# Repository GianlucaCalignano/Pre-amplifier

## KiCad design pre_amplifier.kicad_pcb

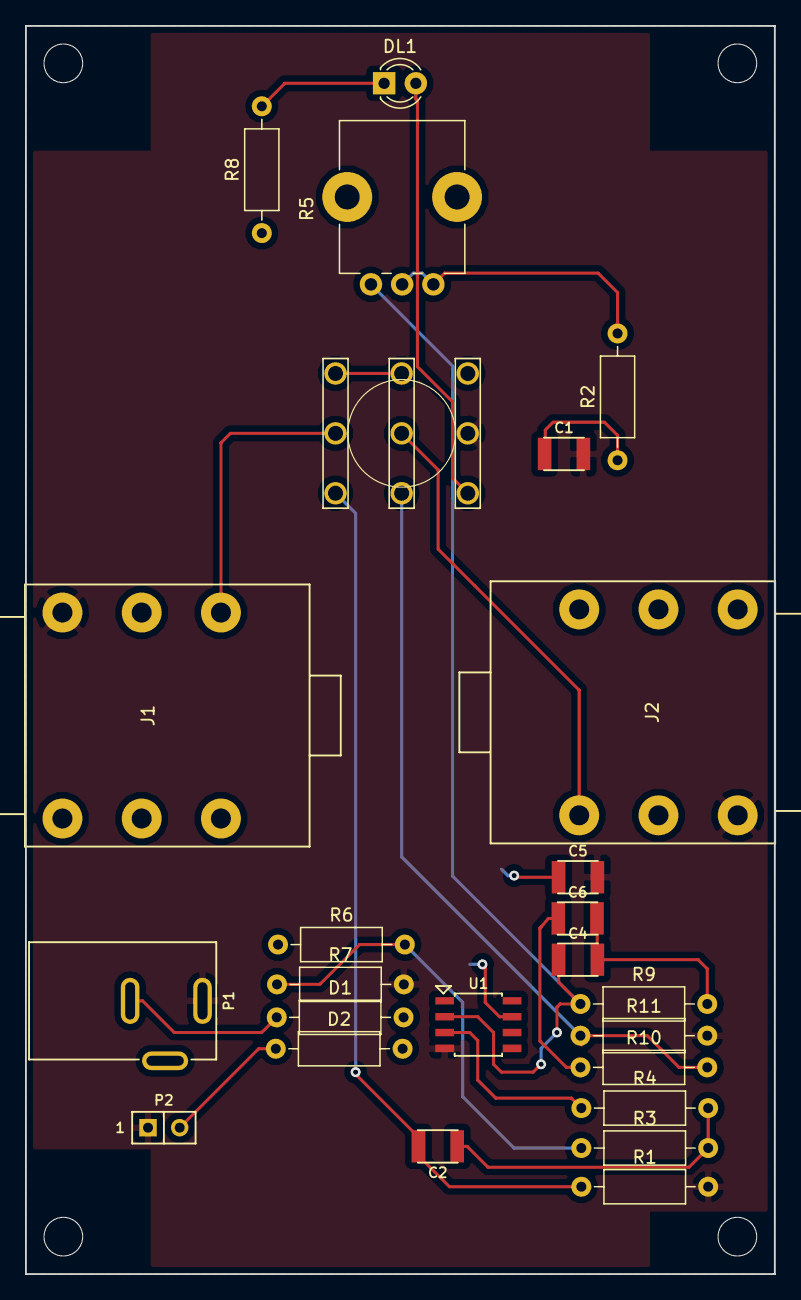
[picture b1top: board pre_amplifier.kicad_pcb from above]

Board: 2 copper layers, 60.0 x 100.0 mm, 25 parts (0 on the bottom side), 19 nets.

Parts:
C1: 4.7uF; CAPACITOR-1210
C2: 0.1uF; CAPACITOR-1210
C4: 47p; CAPACITOR-1210
C5: 100n; CAPACITOR-1210
C6: 15uF; CAPACITOR-1210
D1, D2: 1N4001; R_Axial_DIN0207_L6.3mm_D2.5mm_P10.16mm_Horizontal
DL1: RED; LED_D3.0mm
J1, J2: AudioJack3_Switch; CL12327
P1: BATT_JACK; BARRELJACK-WE-694106301002
P2: CONN_2X1; CONN-STRIP-2x1-2.54
R1: 22M; R_Axial_DIN0207_L6.3mm_D2.5mm_P10.16mm_Horizontal
R2: 2.7K; R_Axial_DIN0207_L6.3mm_D2.5mm_P10.16mm_Horizontal
R3: 10M; R_Axial_DIN0207_L6.3mm_D2.5mm_P10.16mm_Horizontal
R4: 1K; R_Axial_DIN0207_L6.3mm_D2.5mm_P10.16mm_Horizontal
R5: 500K; Potentiometer_Alps_RK09K_Single_Vertical
R6, R7: 100K; R_Axial_DIN0207_L6.3mm_D2.5mm_P10.16mm_Horizontal
R8: RESISTOR; R_Axial_DIN0207_L6.3mm_D2.5mm_P10.16mm_Horizontal
R9: 56k; R_Axial_DIN0207_L6.3mm_D2.5mm_P10.16mm_Horizontal
R10: 470; R_Axial_DIN0207_L6.3mm_D2.5mm_P10.16mm_Horizontal
R11: 10K; R_Axial_DIN0207_L6.3mm_D2.5mm_P10.16mm_Horizontal
S1: SWITCH-3PDT; STOMP-SWITCH-3PDT
U1: TL061; SOIC8_3.9x4.9_1.27

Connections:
+V: C5.1, D1.2, D2.2, R6.1, R8.1, U1.7
+VBAT: D2.1, P2.2
/4V5: R3.1, R6.2, R7.1
/led-: DL1.2, S1.P$9
/sgnIN: C2.2, R1.1, S1.P$3
/sgnOUT: R10.2, R11.1, S1.P$6
/tipIN: J1.6, S1.P$2
/tipOUT: J2.6, S1.P$5
GND: C1.2, C5.2, J1.4, J2.4, P1.1, P2.1, R1.2, R7.2, R11.2, S1.P$8, U1.4
unnamed: C1.1, R2.1
unnamed: C2.1, R3.2, R4.2
unnamed: C4.1, R5.3, R9.1, U1.2
unnamed: C4.2, C6.2, R9.2
unnamed: C6.1, R10.1
unnamed: D1.1, P1.2
unnamed: DL1.1, R8.2
unnamed: R2.2, R5.1, R5.2
unnamed: R4.1, U1.3
unnamed: S1.P$1, S1.P$4

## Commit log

2018-11-06 Added nowae kicad library configuration files
2018-11-06 Added kicad project files
2018-11-06 Added some custom footprint
2018-11-06 Added custom symbols
2018-11-06 Added BOM
2018-11-08 Fixed custom library name
2018-11-08 Changed resistor footprint from SMD to THT
2018-11-08 Added net list file
2018-11-08 Fixed PCB with changed footprints
2018-11-08 Fixed schematic and association footprints
2018-11-08 Updated fp-lib-table with official library
